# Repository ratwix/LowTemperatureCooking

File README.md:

LowTemperatureCooking
=====================

Low temperature cooking

Target of this project is to create a Low temperature cooker based on Arduino Teensy 3.

Goal is to heat water to a specific temperature just perfect for cooking the specific dish.
A big amount a pre-set temperature are embeded.

All the temperatures and time cooking comes from "Modernist Cuisine" book.

Main element :
- Teensy3 for main program
- Nokia 5110 for the screen
- DS18B20 for temperature checking
- Rotary encoder to navigate throw menu
- Two button
-- Back / Reset Timer
-- Menu / Validate
- 220V Heat resistor

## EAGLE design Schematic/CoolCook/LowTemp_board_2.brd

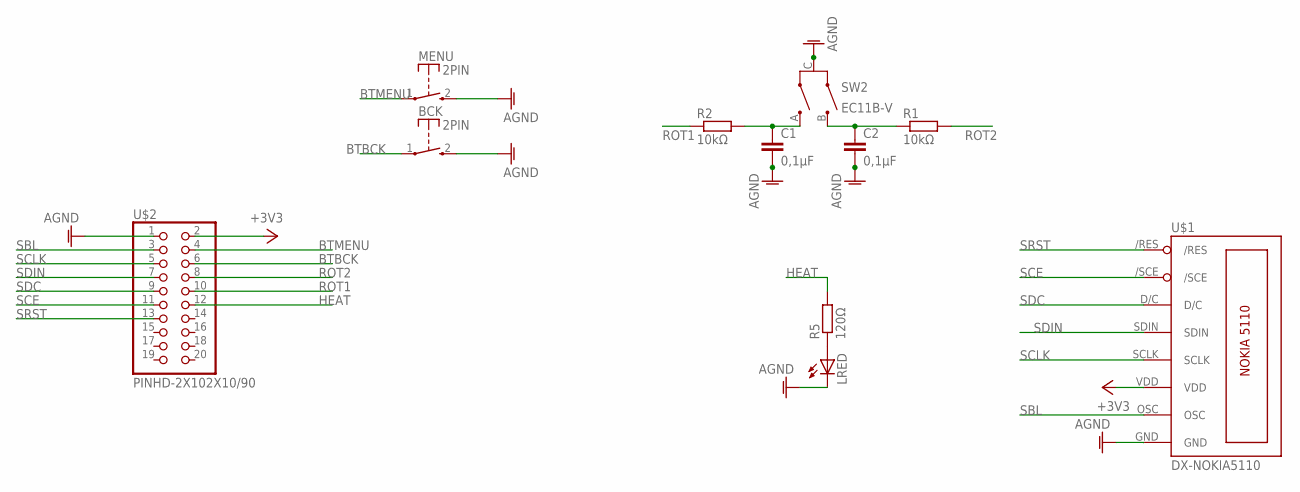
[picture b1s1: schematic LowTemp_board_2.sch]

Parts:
BCK: 2PIN
C1, C2: 0,1µF; C050-025X075
LRED: LED5MM
MENU: 2PIN
R1, R2: 10kΩ; 0207/7
R5: 120Ω; 0207/7
SW2: EC11B-V
U$1: DX-NOKIA5110
U$2: PINHD-2X102X10/90; 2X10/90

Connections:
+3V3: U$1.VDD, U$2.2
AGND: BCK.2 (S), C1.2, C2.2, LRED.K (C), MENU.2 (S), SW2.C, U$1.GND, U$2.1
BTBCK: BCK.1, U$2.6
BTMENU: MENU.1, U$2.4
HEAT: R5.2, U$2.12
unnamed: C1.1, R2.2, SW2.A
unnamed: C2.1, R1.1, SW2.B
unnamed: LRED.A, R5.1
ROT1: R2.1, U$2.10
ROT2: R1.2, U$2.8
SBL: U$1.OSC, U$2.3
SCE: U$1./SCE, U$2.11
SCLK: U$1.SCLK, U$2.5
SDC: U$1.D/C, U$2.9
SDIN: U$1.SDIN, U$2.7
SRST: U$1./RES, U$2.13

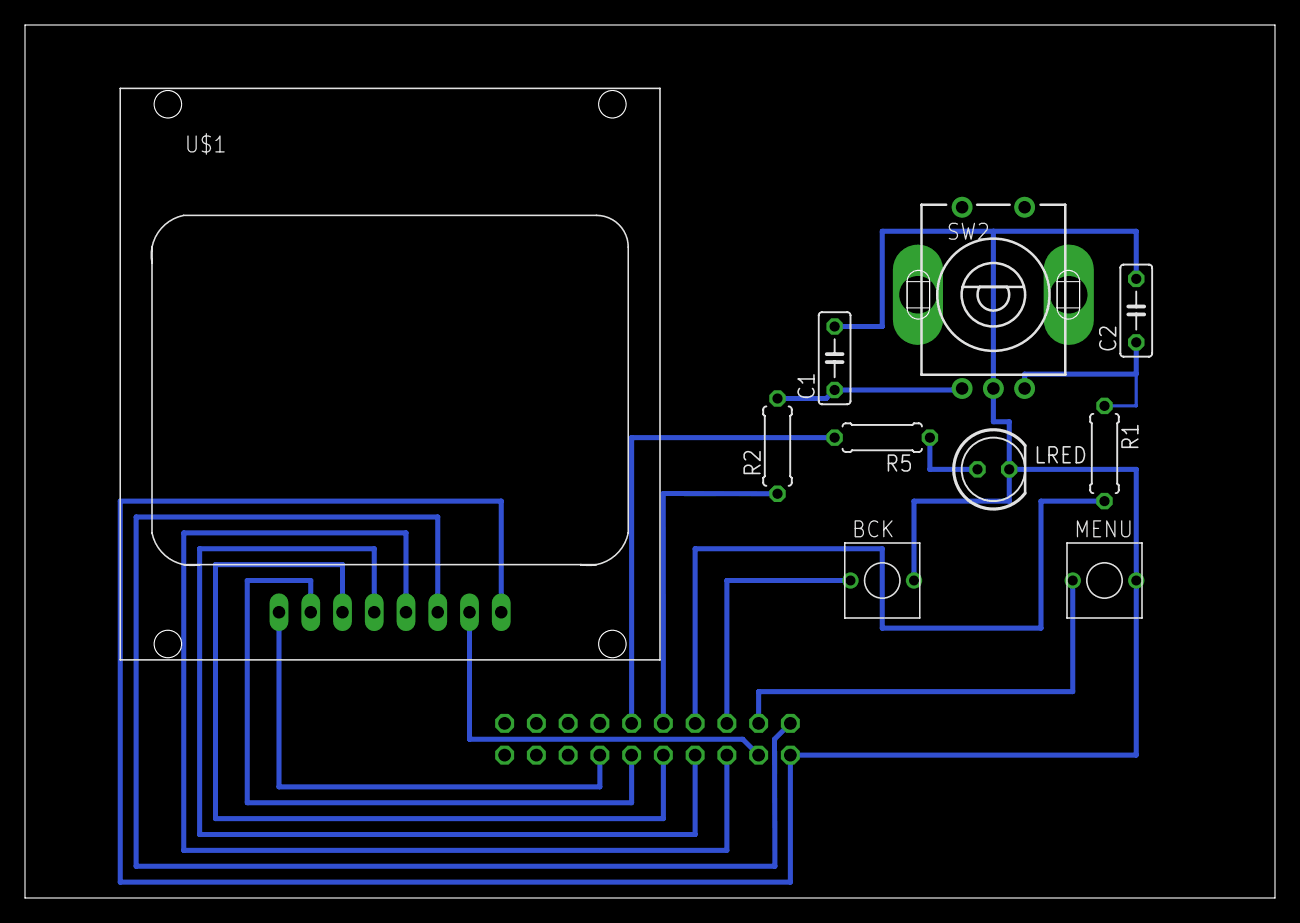
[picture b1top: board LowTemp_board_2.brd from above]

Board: 2 copper layers, 100.0 x 69.8 mm, 11 parts (1 on the bottom side), 16 nets.

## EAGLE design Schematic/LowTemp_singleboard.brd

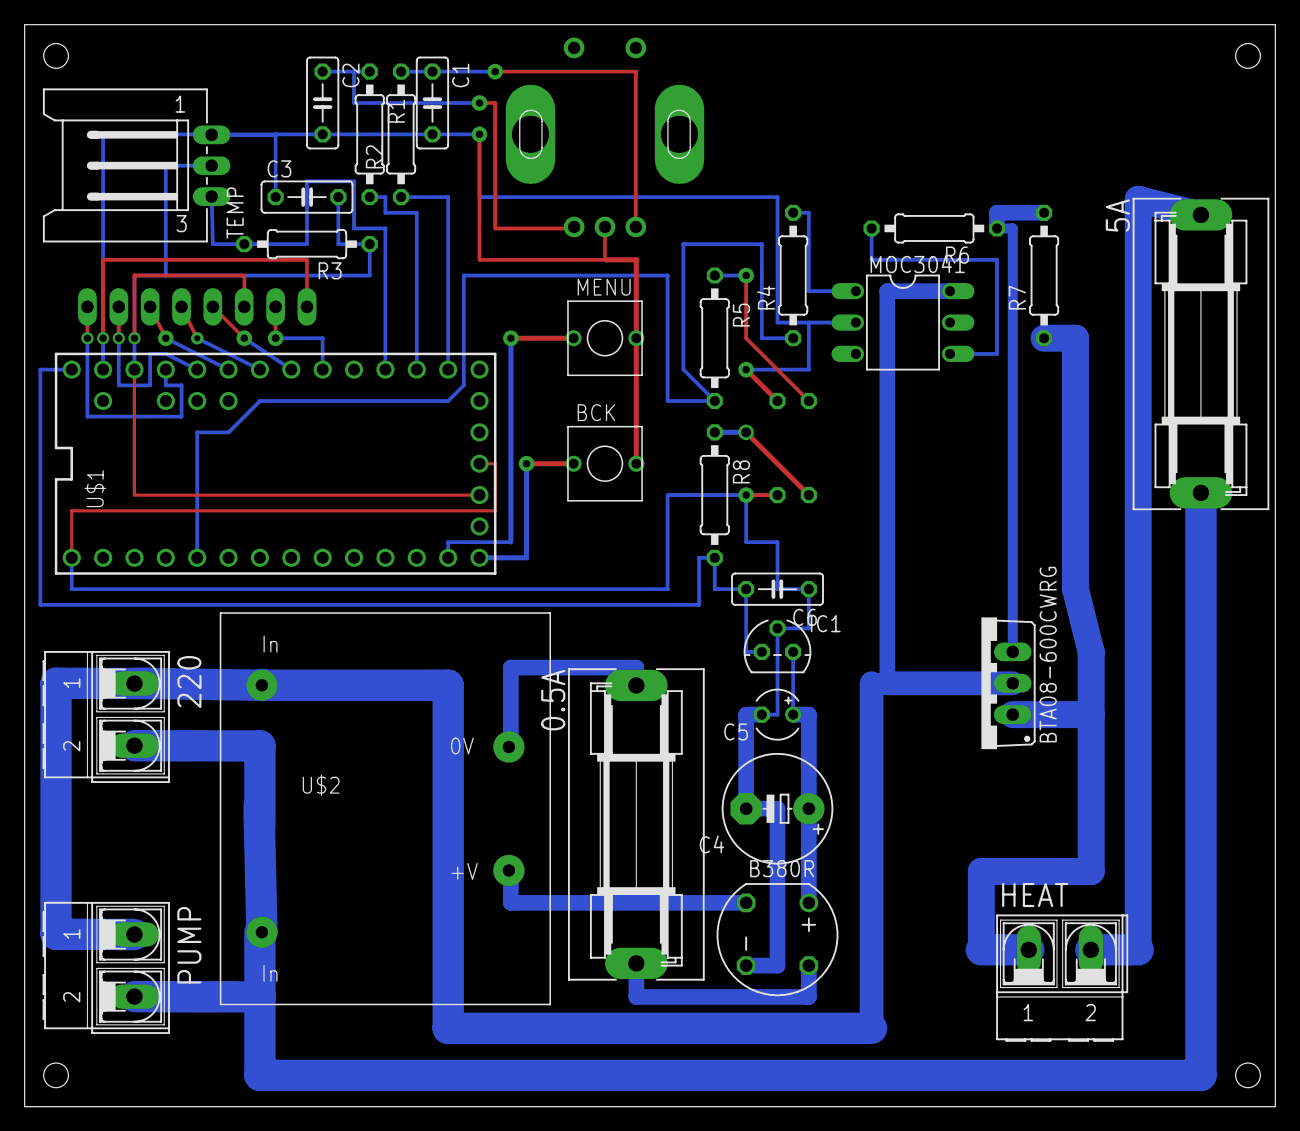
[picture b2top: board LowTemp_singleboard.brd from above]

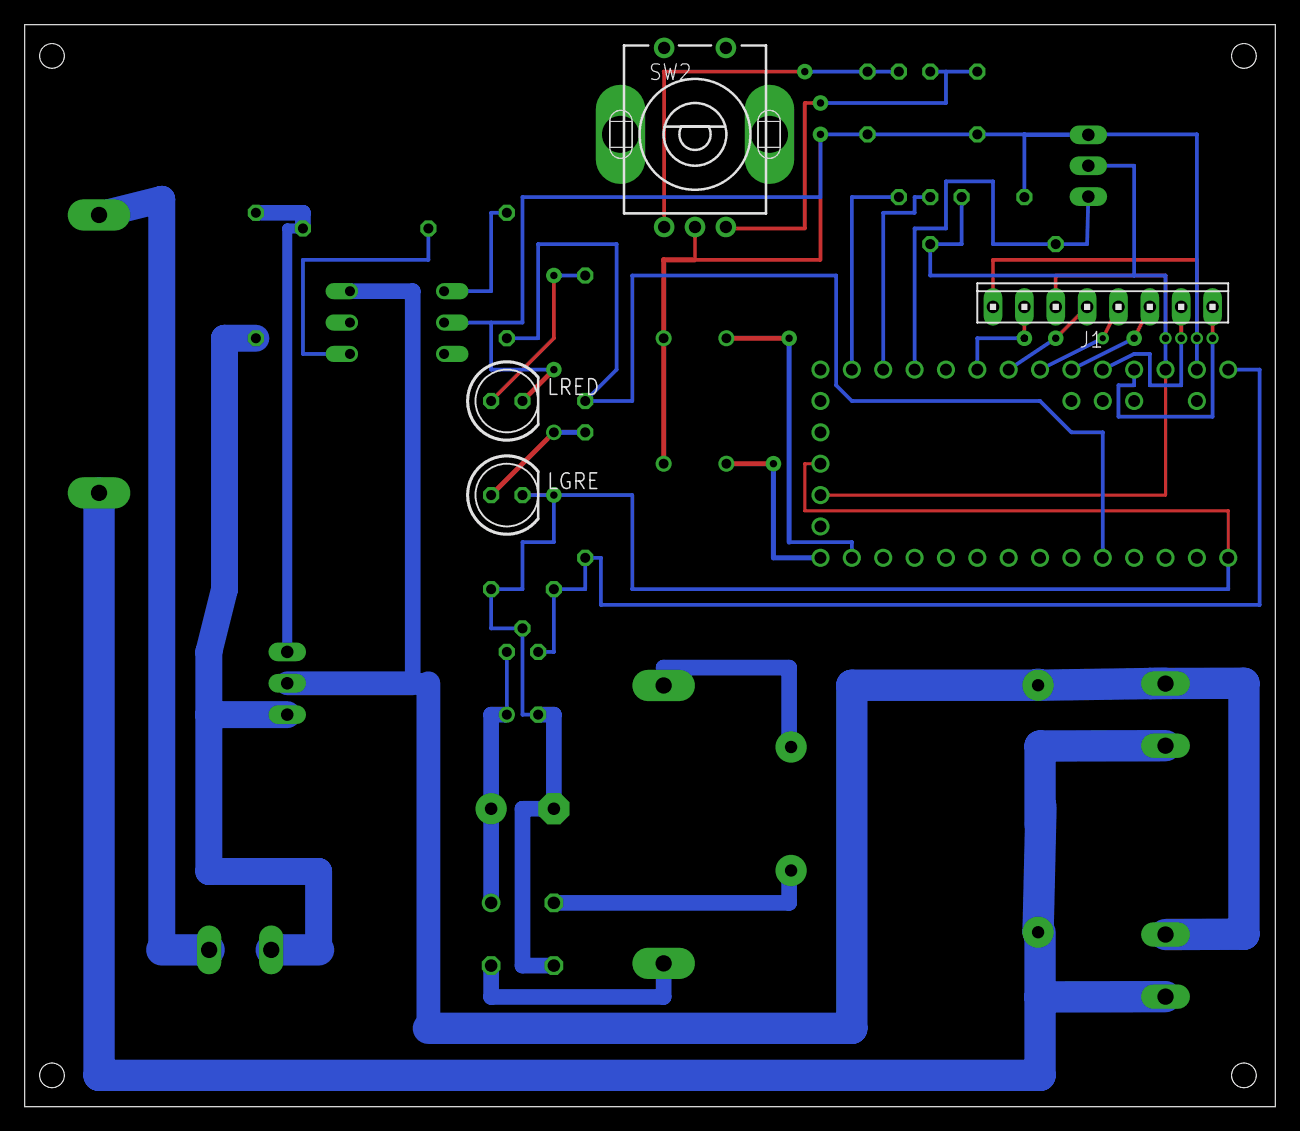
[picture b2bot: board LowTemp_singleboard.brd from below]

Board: 2 copper layers, 101.3 x 87.6 mm, 32 parts (4 on the bottom side), 31 nets.

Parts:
0.5A, 5A: SH22,5A
220: AK500/2-H
B380R: RB1A
BCK: 2PIN
BTA08-600CWRG: BT138-V; TO220BV
C1, C2, C3, C6: 0,1µF; C050-025X075
C4: 470µF; E5-8,5
C5: 3,3µF; TT2D4
HEAT: AK500/2-H
IC1: 7805L; TO92
J1: SCREEN; 10X08MTA
LGRE: LED5MM
LRED: LED5MM
MENU: 2PIN
MOC3041: MOC3021M; DIL06
PUMP: AK500/2-H
R1, R2: 10kΩ; 0207/10
R3: 47kΩ; 0207/10
R4: 130Ω; 0207/10
R5: 120Ω; 0207/10
R6: 360Ω; 0207/10
R7: 63Ω; 0207/10
R8: 330Ω; 0207/10
SW2: EC11B-V
TEMP: L03P
U$1: TEENSY_3.0+4
U$2: 1

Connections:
220VA: BTA08-600CWRG.T2, MOC3041.6, PUMP.1, U$2.1
220VC: 5A.2, 220.2, PUMP.2, U$2.5
+3V3: C3.2, J1.6, R3.1, TEMP.2, U$1.3.3V, U$1.3.3V1
+5V: C6.2, IC1.1, R8.2, U$1.VIN
AGND: BCK.2, C1.2, C2.2, C3.1, J1.8, LRED.K, MENU.2, MOC3041.2, SW2.C, TEMP.1, U$1.AGND
BTBCK: BCK.1, U$1.12
BTMENU: MENU.1, U$1.11
GND: B380R.-, C4.-, C5.-, C6.1, IC1.2, LGRE.K, U$1.GND, U$1.GND1
HEAT: R4.1, R5.2, U$1.3
unnamed: C1.1, R2.2, SW2.A
unnamed: C2.1, R1.1, SW2.B
unnamed: MOC3041.1, R4.2
unnamed: LRED.A, R5.1
unnamed: MOC3041.4, R6.2
unnamed: BTA08-600CWRG.G, R6.1, R7.2
unnamed: 0.5A.1, U$2.9
unnamed: BTA08-600CWRG.T1, HEAT.1, R7.1
unnamed: 5A.1, HEAT.2
unnamed: B380R.AC2, U$2.7
unnamed: 0.5A.2, B380R.AC1
unnamed: B380R.+, C4.+, C5.+, IC1.3
unnamed: LGRE.A, R8.1
ROT1: R2.1, U$1.14/A0
ROT2: R1.2, U$1.15/A1
SBL: J1.7, U$1.18/A4
SCE: J1.2, U$1.22/A8
SCLK: J1.5, U$1.19/A5
SDC: J1.3, U$1.21/A7
SDIN: J1.4, U$1.20/A6
SRST: J1.1, U$1.23/A9
TEMP: R3.2, TEMP.3, U$1.16/A2

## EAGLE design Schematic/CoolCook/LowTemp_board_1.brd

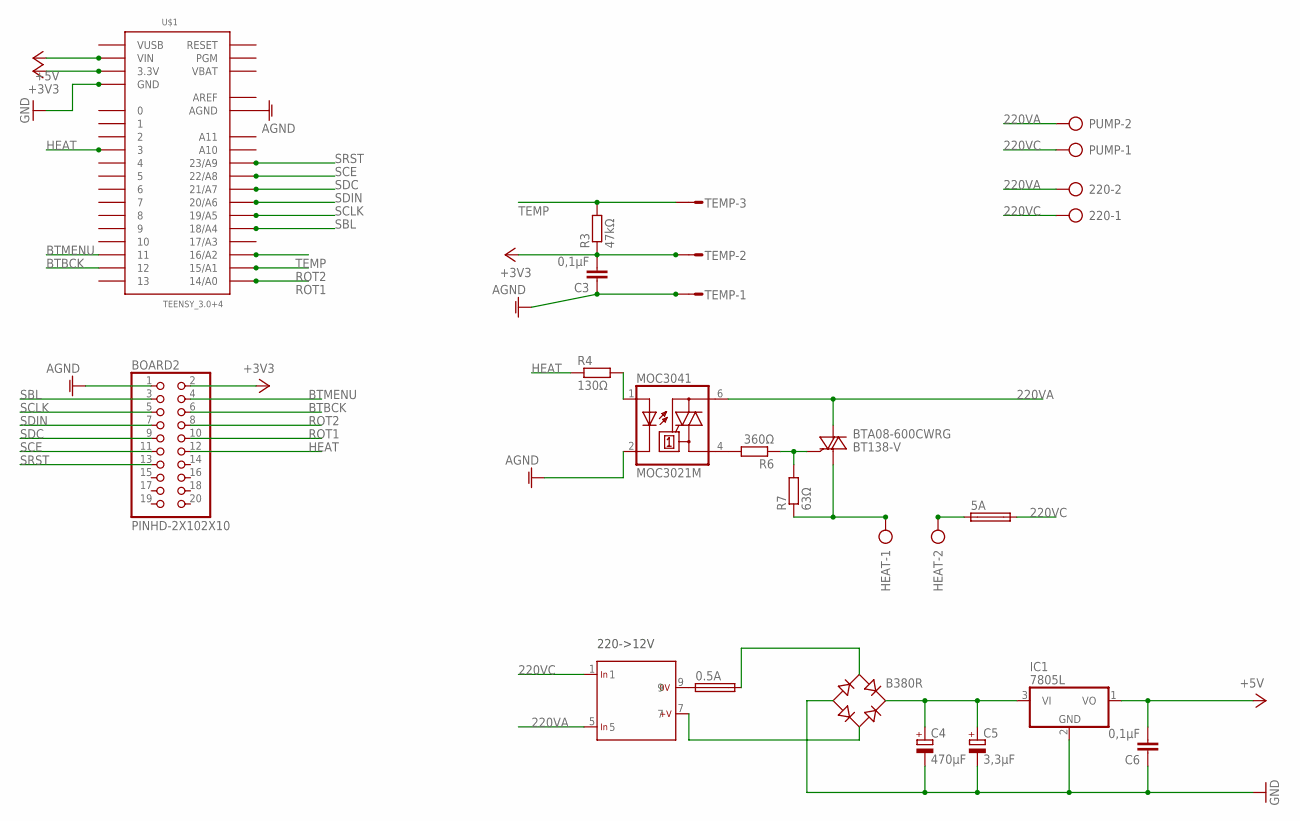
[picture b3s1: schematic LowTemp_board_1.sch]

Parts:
0.5A, 5A: SH22,5A
220: AK500/2-H
220->12V: SINGLE; 1
B380R: RB1A
BOARD2: PINHD-2X102X10; 2X10
BTA08-600CWRG: BT138-V; TO220BV
C3, C6: 0,1µF; C050-025X075
C4: 470µF; E5-8,5
C5: 3,3µF; TT2D4
HEAT: AK500/2-H
IC1: 7805L; TO92
MOC3041: MOC3021M; DIL06
PUMP: AK500/2-H
R3: 47kΩ; 0207/7
R4: 130Ω; 0207/7
R6: 360Ω; 0207/7
R7: 63Ω; 0207/7
TEMP: S03P
U$1: TEENSY_3.0+4

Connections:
220VA: 220.2, 220->12V.5, BTA08-600CWRG.T2 (A2), MOC3041.6 (A2), PUMP.2
220VC: 5A.2, 220.1, 220->12V.1, PUMP.1
+3V3: BOARD2.2, C3.2, R3.1, TEMP.2, U$1.3.3V, U$1.3.3V1 (3.3V)
+5V: C6.2, IC1.1 (VO), U$1.VIN
AGND: BOARD2.1, C3.1, MOC3041.2 (C), TEMP.1, U$1.AGND
AREF: U$1.AREF
BTBCK: BOARD2.6, U$1.12
BTMENU: BOARD2.4, U$1.11
GND: B380R.-, C4.-, C5.-, C6.1, IC1.2 (GND), U$1.GND, U$1.GND1 (GND)
HEAT: BOARD2.12, R4.1, U$1.3
unnamed: MOC3041.1 (A), R4.2
unnamed: MOC3041.4 (A1), R6.2
unnamed: BTA08-600CWRG.G, R6.1, R7.2
unnamed: 0.5A.1, 220->12V.9
unnamed: BTA08-600CWRG.T1 (A1), HEAT.1, R7.1
unnamed: 5A.1, HEAT.2
unnamed: 220->12V.7, B380R.AC2
unnamed: 0.5A.2, B380R.AC1
unnamed: B380R.+, C4.+, C5.+, IC1.3 (VI)
ROT1: BOARD2.10, U$1.14/A0
ROT2: BOARD2.8, U$1.15/A1
SBL: BOARD2.3, U$1.18/A4
SCE: BOARD2.11, U$1.22/A8
SCLK: BOARD2.5, U$1.19/A5
SDC: BOARD2.9, U$1.21/A7
SDIN: BOARD2.7, U$1.20/A6
SRST: BOARD2.13, U$1.23/A9
TEMP: R3.2, TEMP.3, U$1.16/A2
VBAT: U$1.VBAT
VUSB: U$1.VUSB

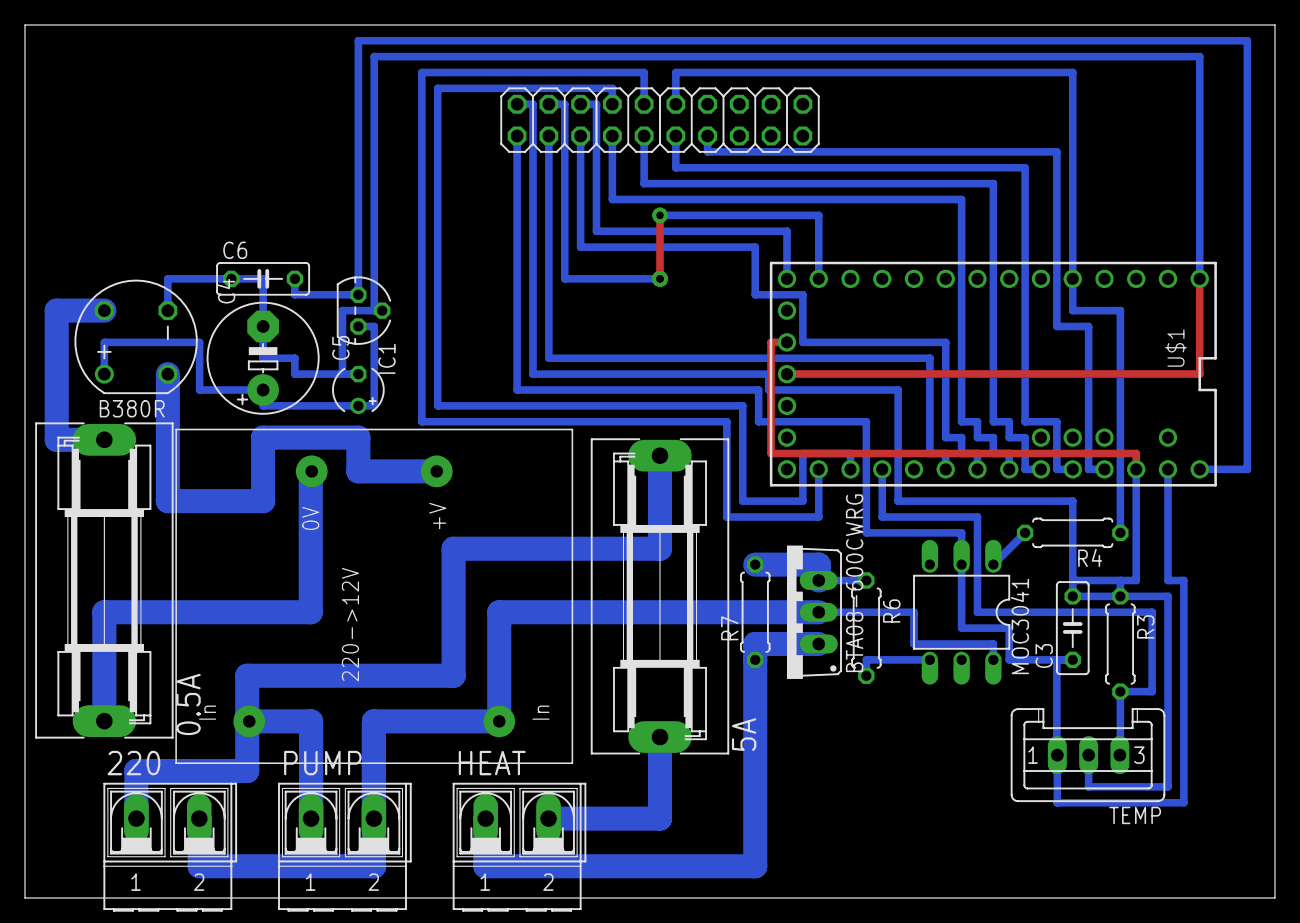
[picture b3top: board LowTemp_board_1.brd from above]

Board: 2 copper layers, 100.0 x 69.8 mm, 21 parts (0 on the bottom side), 27 nets.

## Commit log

2013-05-22 First commit Arduino file
2013-05-24 Add scrolling text Rename temperature.h to menu.h Complete menu.h (missing hard meets)
2013-05-24 Complete README.md Move files
2013-05-24 Complete menu.h file with all dish Sort them by alphabetic order (french) Add heat connection on pin 3 (heat when temperature too low)
2013-06-03 Optimize Rotary encoder Correct menu.h Add a splashscreen logo
2013-06-04 Add Schematics
2013-06-07 Add 2 board schematic. One board for the controls (screen / button) One board for electronics part
    Each board areBoards are connected together with 2x10 pin connector
2013-06-13 Update schematic in two boards (test and work great) Reverse rotation in arduino program
